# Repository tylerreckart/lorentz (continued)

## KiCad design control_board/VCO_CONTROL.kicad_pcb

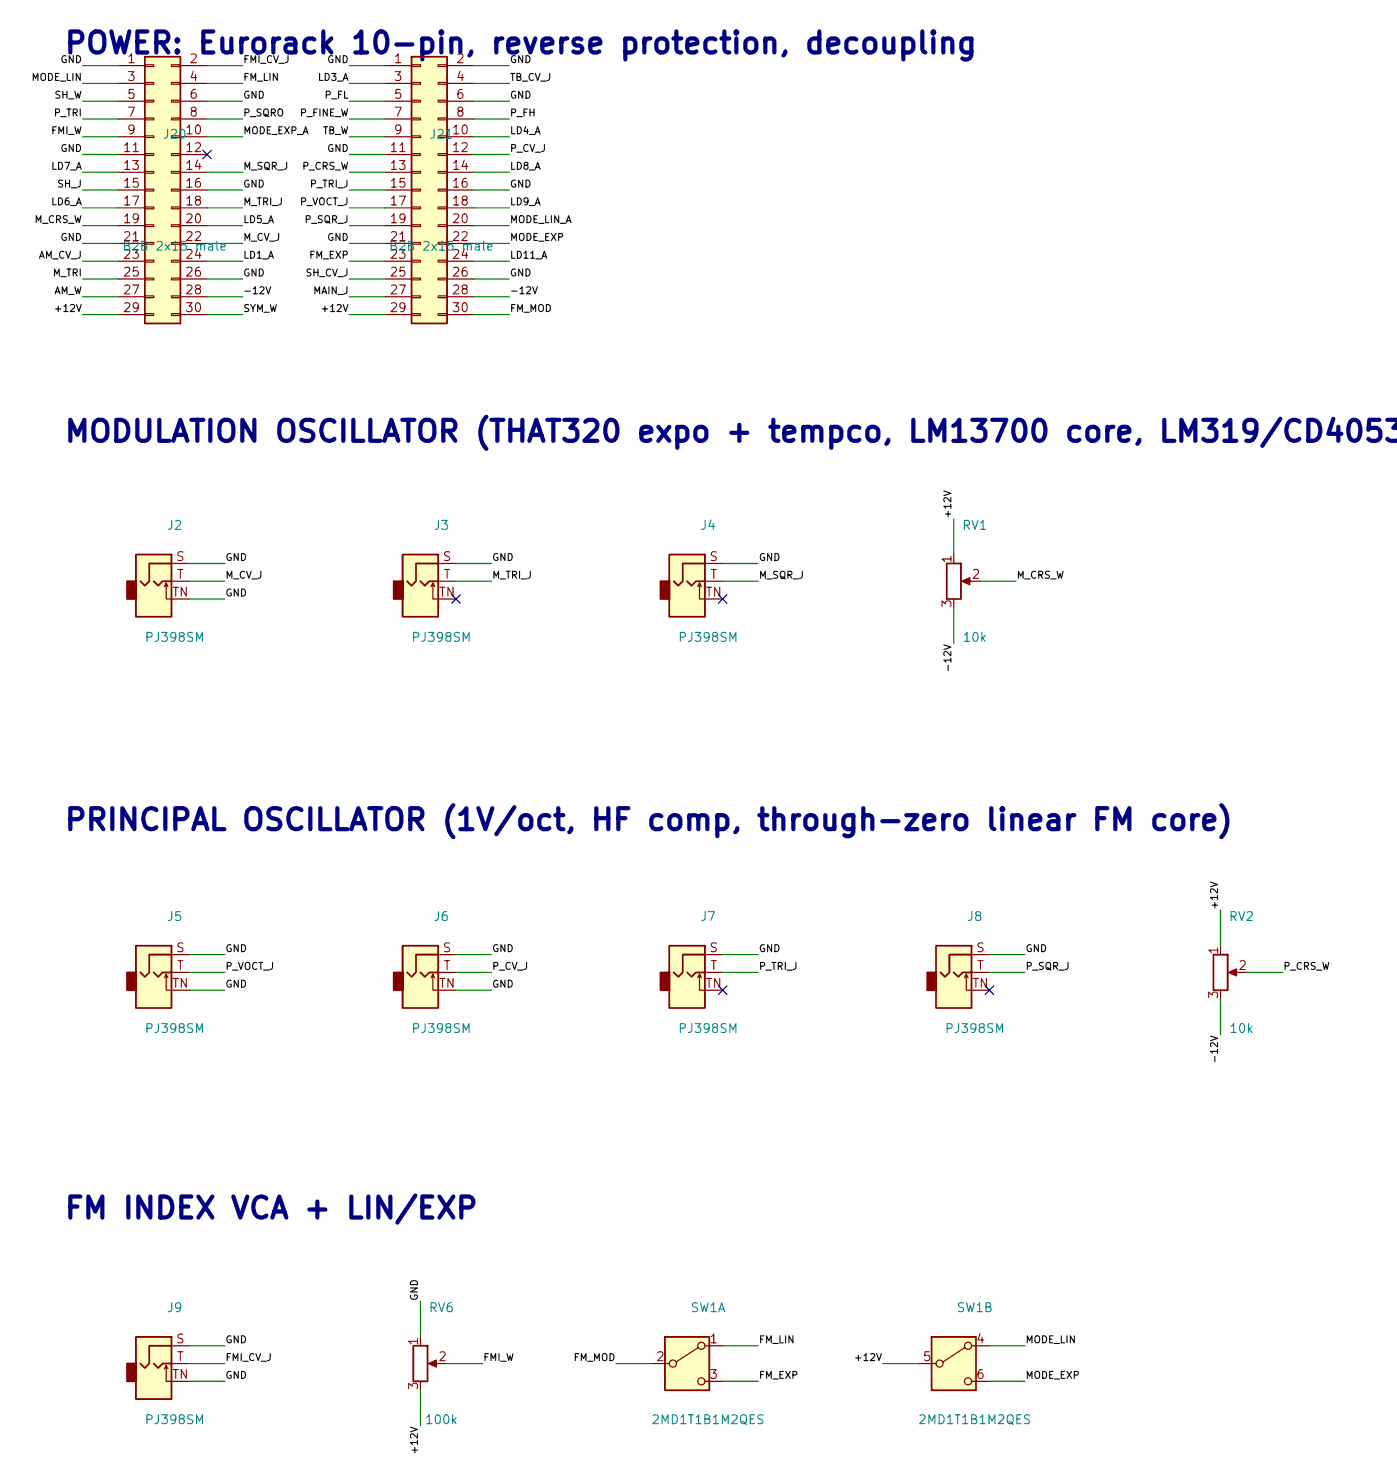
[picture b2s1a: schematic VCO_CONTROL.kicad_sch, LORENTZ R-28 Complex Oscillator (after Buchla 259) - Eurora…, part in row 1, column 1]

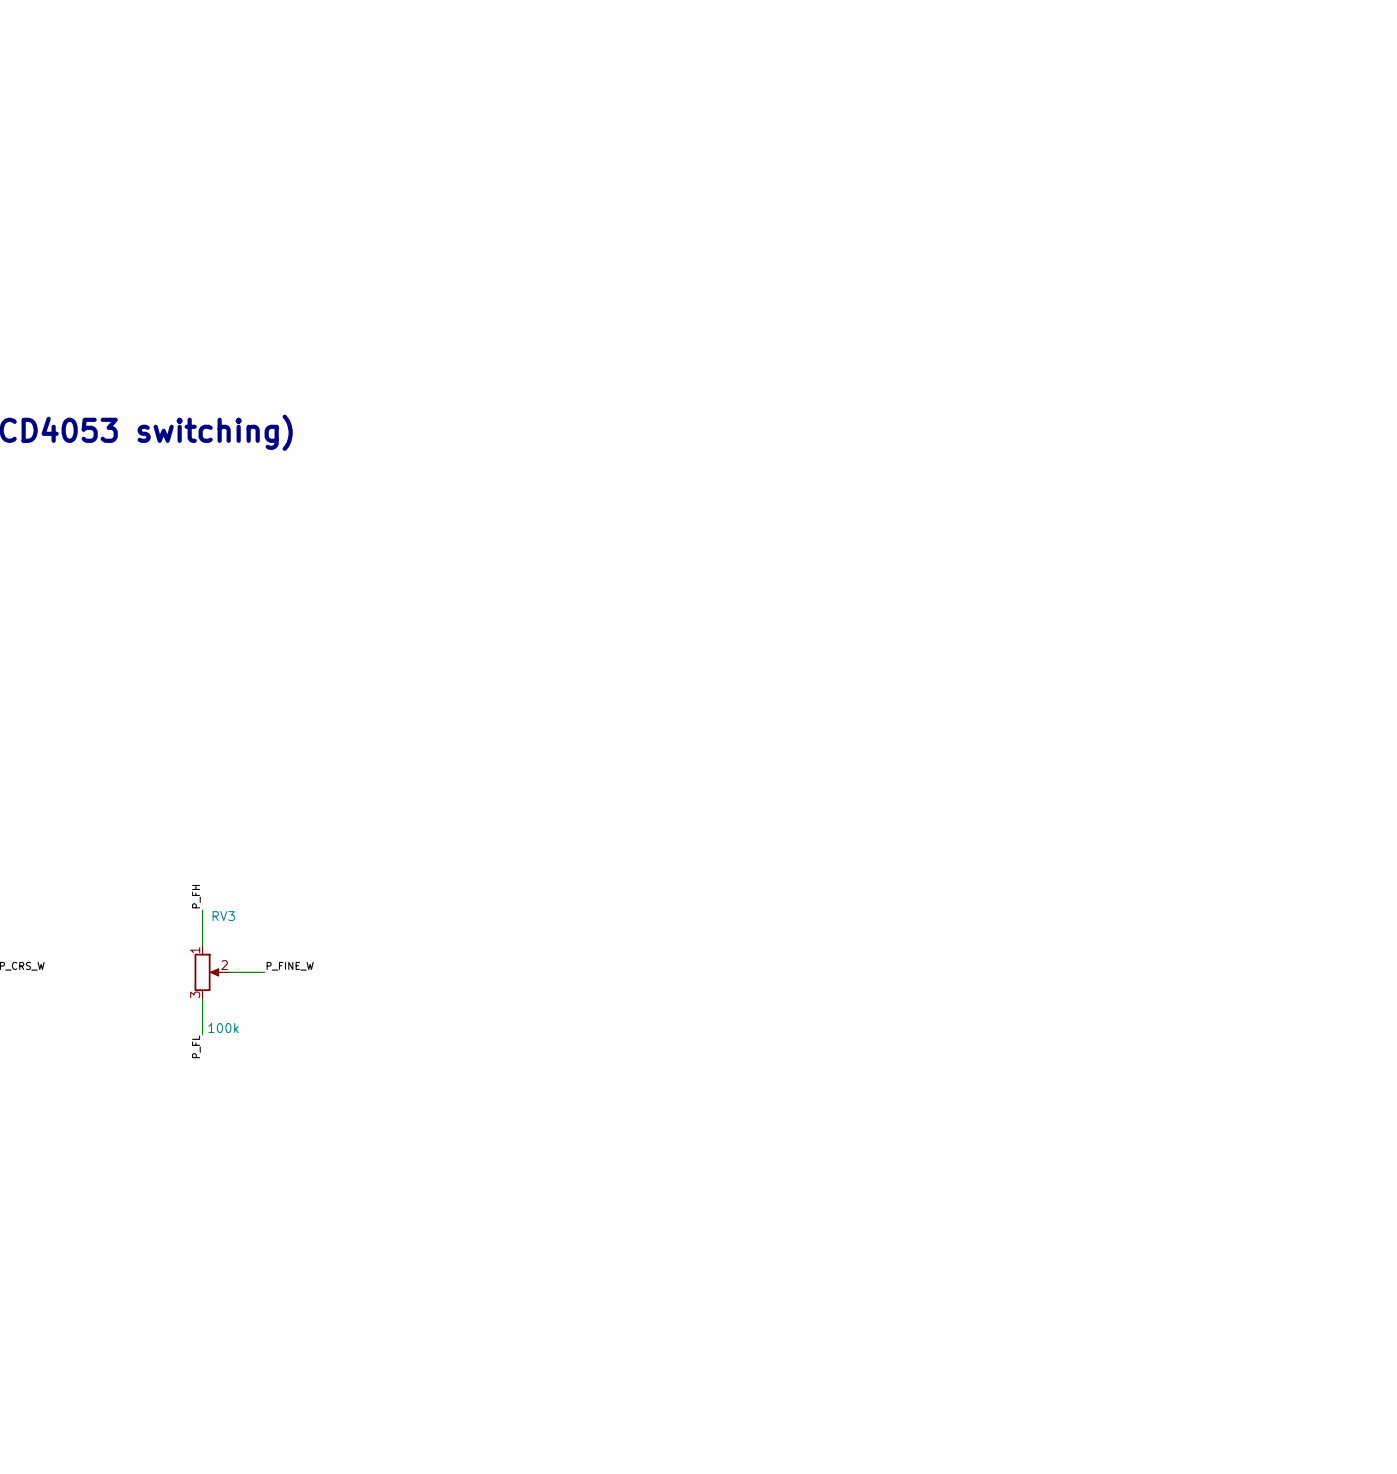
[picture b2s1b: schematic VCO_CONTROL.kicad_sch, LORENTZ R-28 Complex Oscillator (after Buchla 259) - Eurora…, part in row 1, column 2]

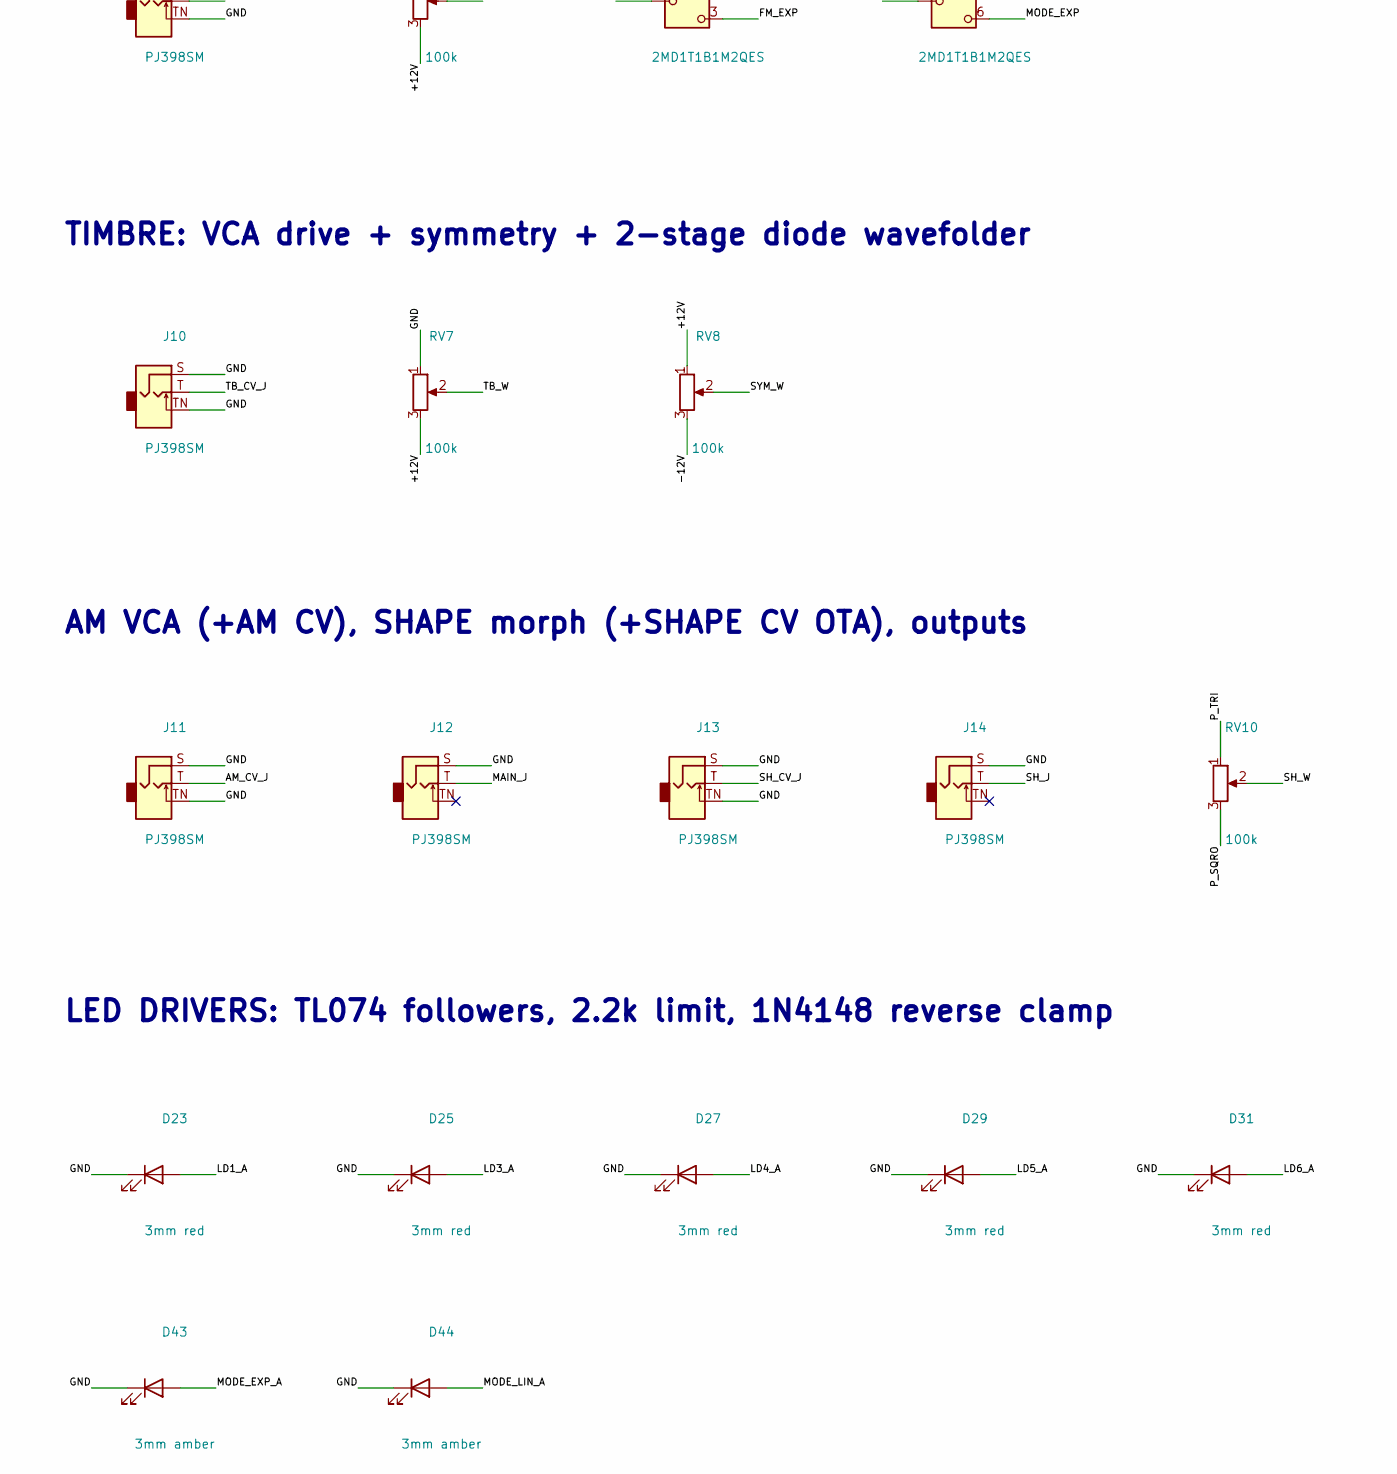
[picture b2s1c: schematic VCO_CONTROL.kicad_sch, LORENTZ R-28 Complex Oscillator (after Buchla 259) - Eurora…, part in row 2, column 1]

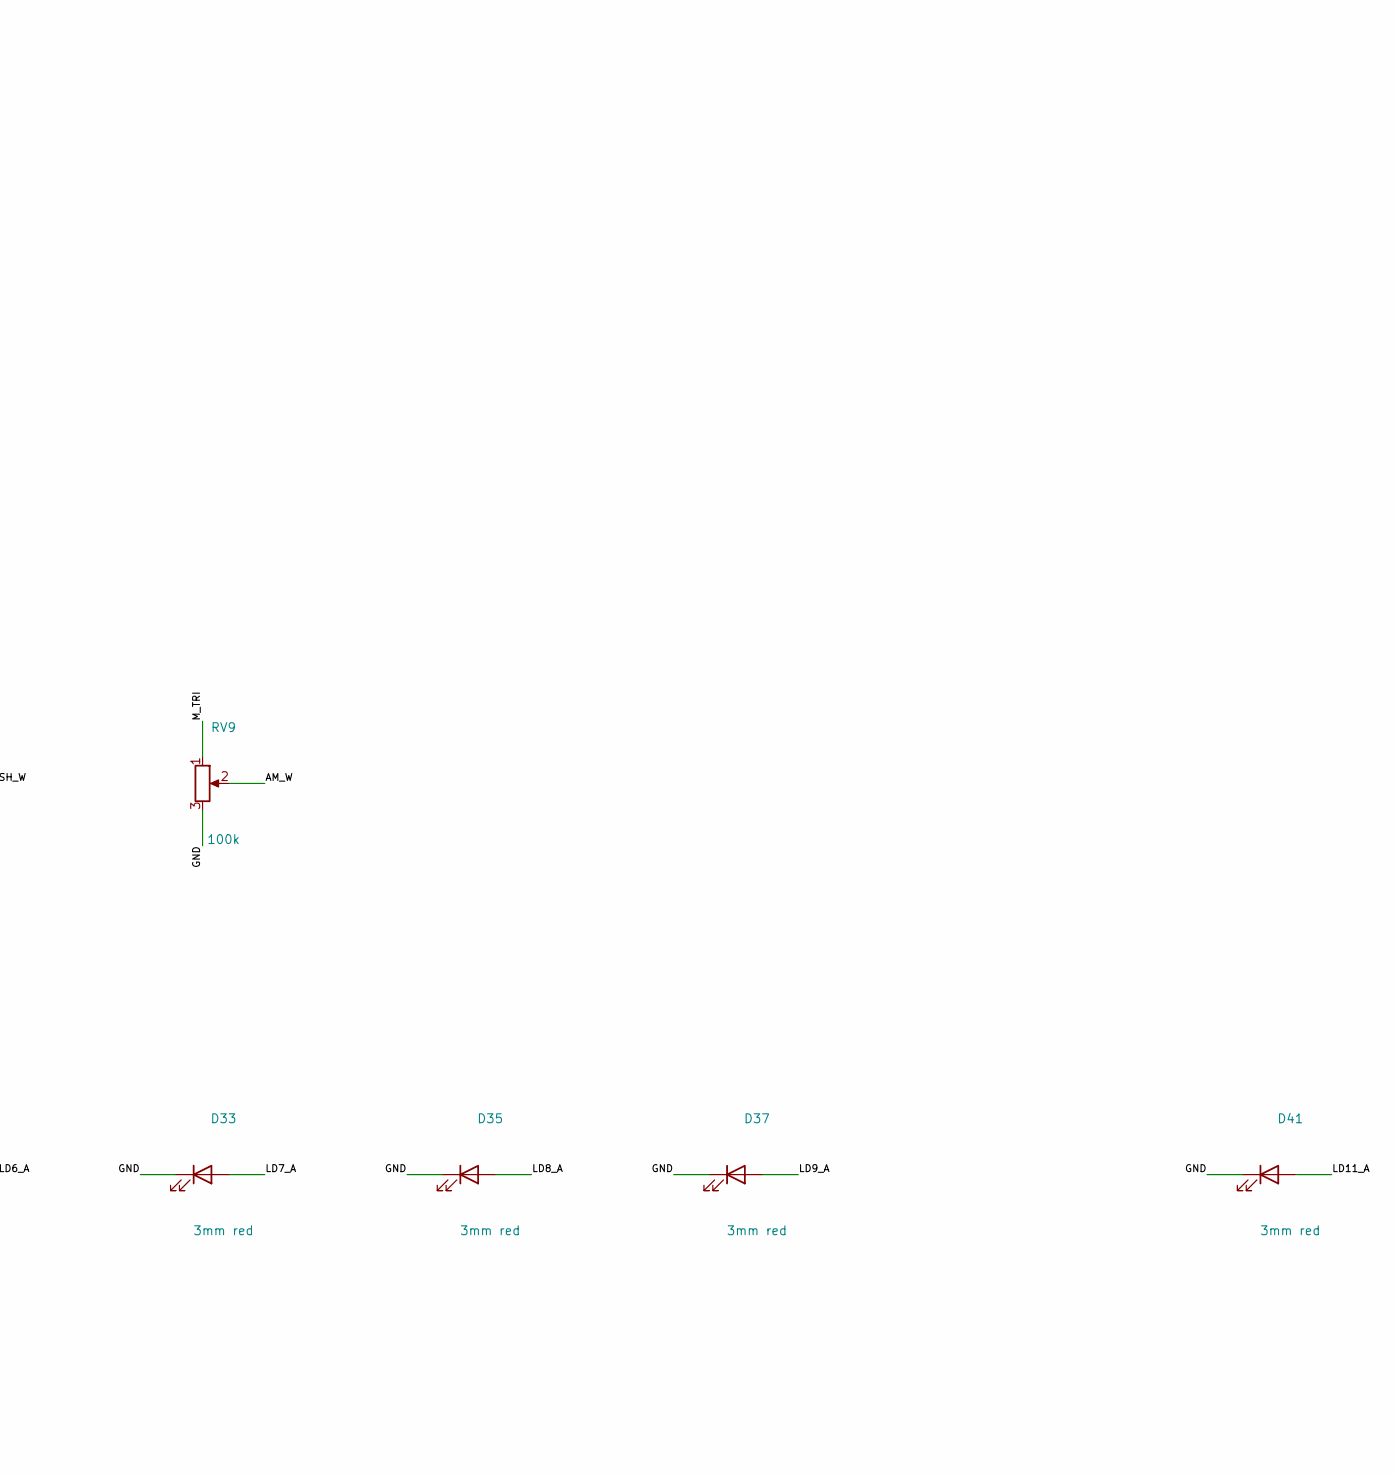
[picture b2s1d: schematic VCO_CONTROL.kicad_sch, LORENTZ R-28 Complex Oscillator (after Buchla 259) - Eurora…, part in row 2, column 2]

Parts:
D23, D25, D27, D29, D31, D33, D35, D37, D41: 3mm red; LED_D3.0mm
D43, D44: 3mm amber; LED_D3.0mm
J2, J3, J4, J5, J6, J7, J8, J9, J10, J11, J12, J13, J14: PJ398SM; Jack_3.5mm_QingPu_WQP-PJ398SM_Vertical_CircularHoles
J20, J21: B2B 2x15 male; PinHeader_2x15_P2.54mm_Vertical
RV1, RV2: 10k; Alpha_RV16AF-41_Single_Vertical
RV3, RV6, RV7, RV8, RV9, RV10: 100k; Potentiometer_Alpha_RD901F-40-00D_Single_Vertical
SW1: 2MD1T1B1M2QES; SW_Dailywell_2MD1_M2

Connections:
/+12V: J20.29, J21.29, RV1.1, RV2.1, RV6.3, RV7.3, RV8.1, SW1.5 (B)
/-12V: J20.28, J21.28, RV1.3, RV2.3, RV8.3
/AM_CV_J: J11.T, J20.23
/AM_W: J20.27, RV9.2
/FMI_CV_J: J9.T, J20.2
/FMI_W: J20.9, RV6.2
/FM_EXP: J21.23, SW1.3 (C)
/FM_LIN: J20.4, SW1.1 (A)
/FM_MOD: J21.30, SW1.2 (B)
/GND: D23.1 (K), D25.1 (K), D27.1 (K), D29.1 (K), D31.1 (K), D33.1 (K), D35.1 (K), D37.1 (K), D41.1 (K), D43.1 (K), D44.1 (K), J2.S, J2.TN, J3.S, J4.S, J5.S, J5.TN, J6.S, J6.TN, J7.S, J8.S, J9.S, J9.TN, J10.S, J10.TN, J11.S, J11.TN, J12.S, J13.S, J13.TN, J14.S, J20.1, J20.6, J20.11, J20.16, J20.21, J20.26, J21.1, J21.2, J21.6, J21.11, J21.16, J21.21, J21.26, RV6.1, RV7.1, RV9.3
/LD1_A: D23.2 (A), J20.24
/LD3_A: D25.2 (A), J21.3
/LD4_A: D27.2 (A), J21.10
/LD5_A: D29.2 (A), J20.20
/LD6_A: D31.2 (A), J20.17
/LD7_A: D33.2 (A), J20.13
/LD8_A: D35.2 (A), J21.14
/LD9_A: D37.2 (A), J21.18
/LD11_A: D41.2 (A), J21.24
/MAIN_J: J12.T, J21.27
/MODE_EXP: J21.22, SW1.6 (C)
/MODE_EXP_A: D43.2 (A), J20.10
/MODE_LIN: J20.3, SW1.4 (A)
/MODE_LIN_A: D44.2 (A), J21.20
/M_CRS_W: J20.19, RV1.2
/M_CV_J: J2.T, J20.22
/M_SQR_J: J4.T, J20.14
/M_TRI: J20.25, RV9.1
/M_TRI_J: J3.T, J20.18
/P_CRS_W: J21.13, RV2.2
/P_CV_J: J6.T, J21.12
/P_FH: J21.8, RV3.1
/P_FINE_W: J21.7, RV3.2
/P_FL: J21.5, RV3.3
/P_SQRO: J20.8, RV10.3
/P_SQR_J: J8.T, J21.19
/P_TRI: J20.7, RV10.1
/P_TRI_J: J7.T, J21.15
/P_VOCT_J: J5.T, J21.17
/SH_CV_J: J13.T, J21.25
/SH_J: J14.T, J20.15
/SH_W: J20.5, RV10.2
/SYM_W: J20.30, RV8.2
/TB_CV_J: J10.T, J21.4
/TB_W: J21.9, RV7.2

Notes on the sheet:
POWER: Eurorack 10-pin, reverse protection, decoupling
MODULATION OSCILLATOR (THAT320 expo + tempco, LM13700 core, LM319/CD4053 switching)
PRINCIPAL OSCILLATOR (1V/oct, HF comp, through-zero linear FM core)
FM INDEX VCA + LIN/EXP
TIMBRE: VCA drive + symmetry + 2-stage diode wavefolder
AM VCA (+AM CV), SHAPE morph (+SHAPE CV OTA), outputs
LED DRIVERS: TL074 followers, 2.2k limit, 1N4148 reverse clamp

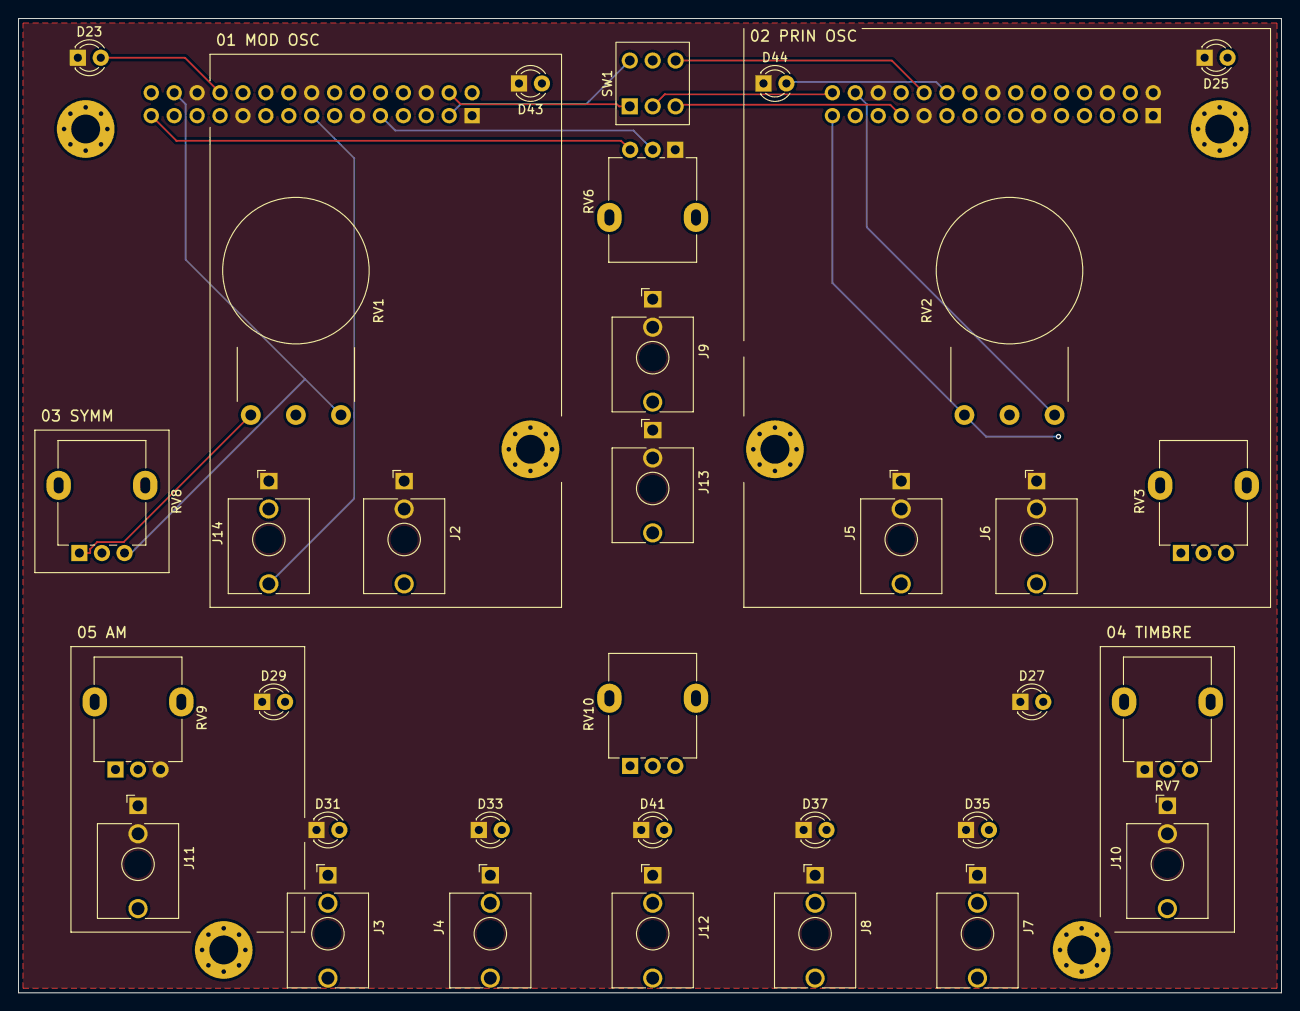
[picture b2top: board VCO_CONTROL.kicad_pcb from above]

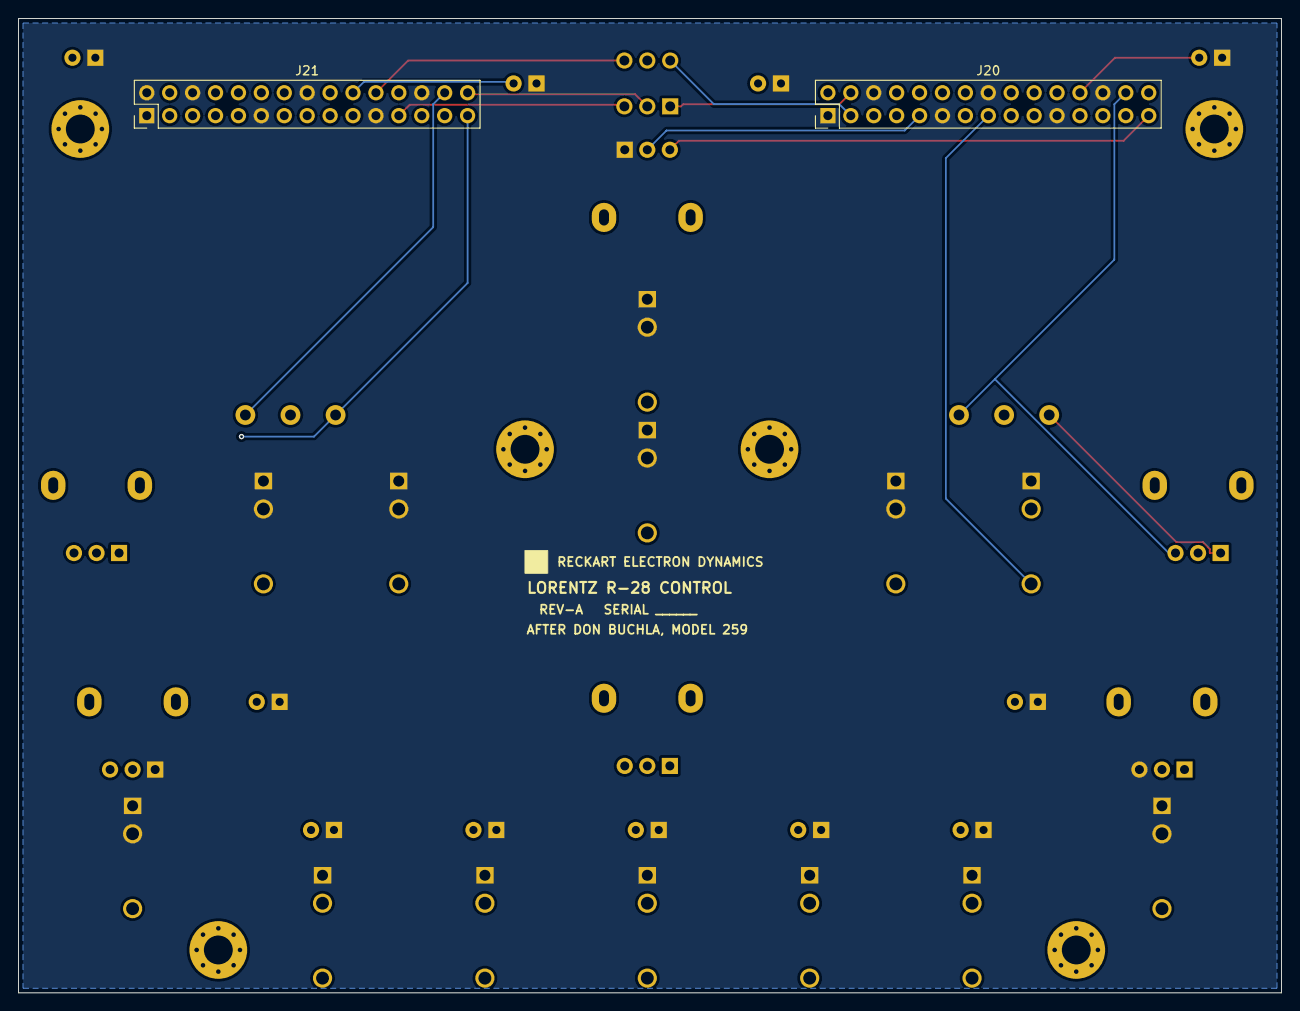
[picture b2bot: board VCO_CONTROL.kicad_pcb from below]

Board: 4 copper layers, 140.0 x 108.0 mm, 41 parts (2 on the bottom side), 45 nets.

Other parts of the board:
H1, H2, H3, H4, H5, H6: M3 standoff; MountingHole_3.2mm_M3_Pad_Via

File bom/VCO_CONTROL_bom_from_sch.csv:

"Refs","Value","Footprint","Qty","DNP"
"D23","3mm red","LED_THT:LED_D3.0mm","1",""
"D25","3mm red","LED_THT:LED_D3.0mm","1",""
"D27","3mm red","LED_THT:LED_D3.0mm","1",""
"D29","3mm red","LED_THT:LED_D3.0mm","1",""
"D31","3mm red","LED_THT:LED_D3.0mm","1",""
"D33","3mm red","LED_THT:LED_D3.0mm","1",""
"D35","3mm red","LED_THT:LED_D3.0mm","1",""
"D37","3mm red","LED_THT:LED_D3.0mm","1",""
"D41","3mm red","LED_THT:LED_D3.0mm","1",""
"D43","3mm amber","LED_THT:LED_D3.0mm","1",""
"D44","3mm amber","LED_THT:LED_D3.0mm","1",""
"J2","PJ398SM","Connector_Audio:Jack_3.5mm_QingPu_WQP-PJ398SM_Vertical_CircularHoles","1",""
"J3","PJ398SM","Connector_Audio:Jack_3.5mm_QingPu_WQP-PJ398SM_Vertical_CircularHoles","1",""
"J4","PJ398SM","Connector_Audio:Jack_3.5mm_QingPu_WQP-PJ398SM_Vertical_CircularHoles","1",""
"J5","PJ398SM","Connector_Audio:Jack_3.5mm_QingPu_WQP-PJ398SM_Vertical_CircularHoles","1",""
"J6","PJ398SM","Connector_Audio:Jack_3.5mm_QingPu_WQP-PJ398SM_Vertical_CircularHoles","1",""
"J7","PJ398SM","Connector_Audio:Jack_3.5mm_QingPu_WQP-PJ398SM_Vertical_CircularHoles","1",""
"J8","PJ398SM","Connector_Audio:Jack_3.5mm_QingPu_WQP-PJ398SM_Vertical_CircularHoles","1",""
"J9","PJ398SM","Connector_Audio:Jack_3.5mm_QingPu_WQP-PJ398SM_Vertical_CircularHoles","1",""
"J10","PJ398SM","Connector_Audio:Jack_3.5mm_QingPu_WQP-PJ398SM_Vertical_CircularHoles","1",""
"J11","PJ398SM","Connector_Audio:Jack_3.5mm_QingPu_WQP-PJ398SM_Vertical_CircularHoles","1",""
"J12","PJ398SM","Connector_Audio:Jack_3.5mm_QingPu_WQP-PJ398SM_Vertical_CircularHoles","1",""
"J13","PJ398SM","Connector_Audio:Jack_3.5mm_QingPu_WQP-PJ398SM_Vertical_CircularHoles","1",""
"J14","PJ398SM","Connector_Audio:Jack_3.5mm_QingPu_WQP-PJ398SM_Vertical_CircularHoles","1",""
"J20","B2B 2x15 male","Connector_PinHeader_2.54mm:PinHeader_2x15_P2.54mm_Vertical","1",""
"J21","B2B 2x15 male","Connector_PinHeader_2.54mm:PinHeader_2x15_P2.54mm_Vertical","1",""
"RV1","10k","VCO25:Alpha_RV16AF-41_Single_Vertical","1",""
"RV2","10k","VCO25:Alpha_RV16AF-41_Single_Vertical","1",""
"RV3","100k","Potentiometer_THT:Potentiometer_Alpha_RD901F-40-00D_Single_Vertical","1",""
"RV6","100k","Potentiometer_THT:Potentiometer_Alpha_RD901F-40-00D_Single_Vertical","1",""
"RV7","100k","Potentiometer_THT:Potentiometer_Alpha_RD901F-40-00D_Single_Vertical","1",""
"RV8","100k","Potentiometer_THT:Potentiometer_Alpha_RD901F-40-00D_Single_Vertical","1",""
"RV9","100k","Potentiometer_THT:Potentiometer_Alpha_RD901F-40-00D_Single_Vertical","1",""
"RV10","100k","Potentiometer_THT:Potentiometer_Alpha_RD901F-40-00D_Single_Vertical","1",""
"SW1","2MD1T1B1M2QES","VCO:SW_Dailywell_2MD1_M2","1",""
